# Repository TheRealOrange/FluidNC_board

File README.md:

# FluidNC_board
board for fluidnc

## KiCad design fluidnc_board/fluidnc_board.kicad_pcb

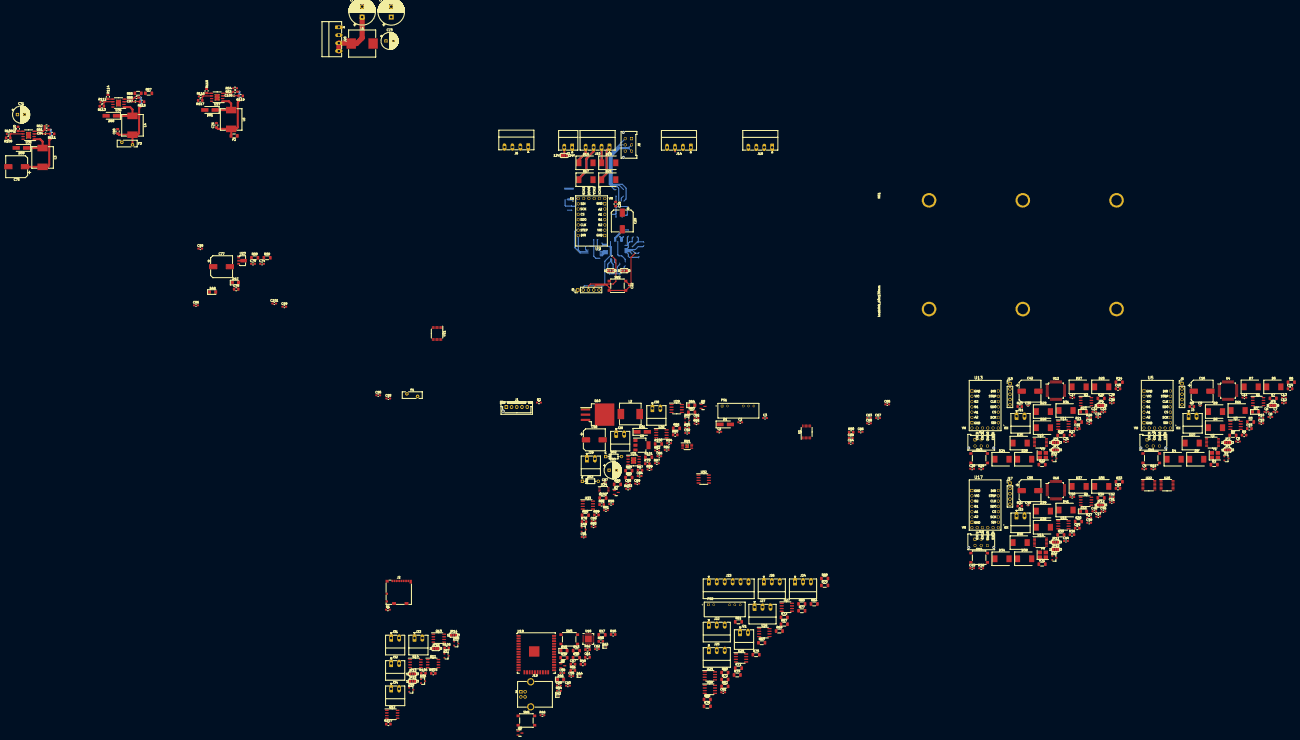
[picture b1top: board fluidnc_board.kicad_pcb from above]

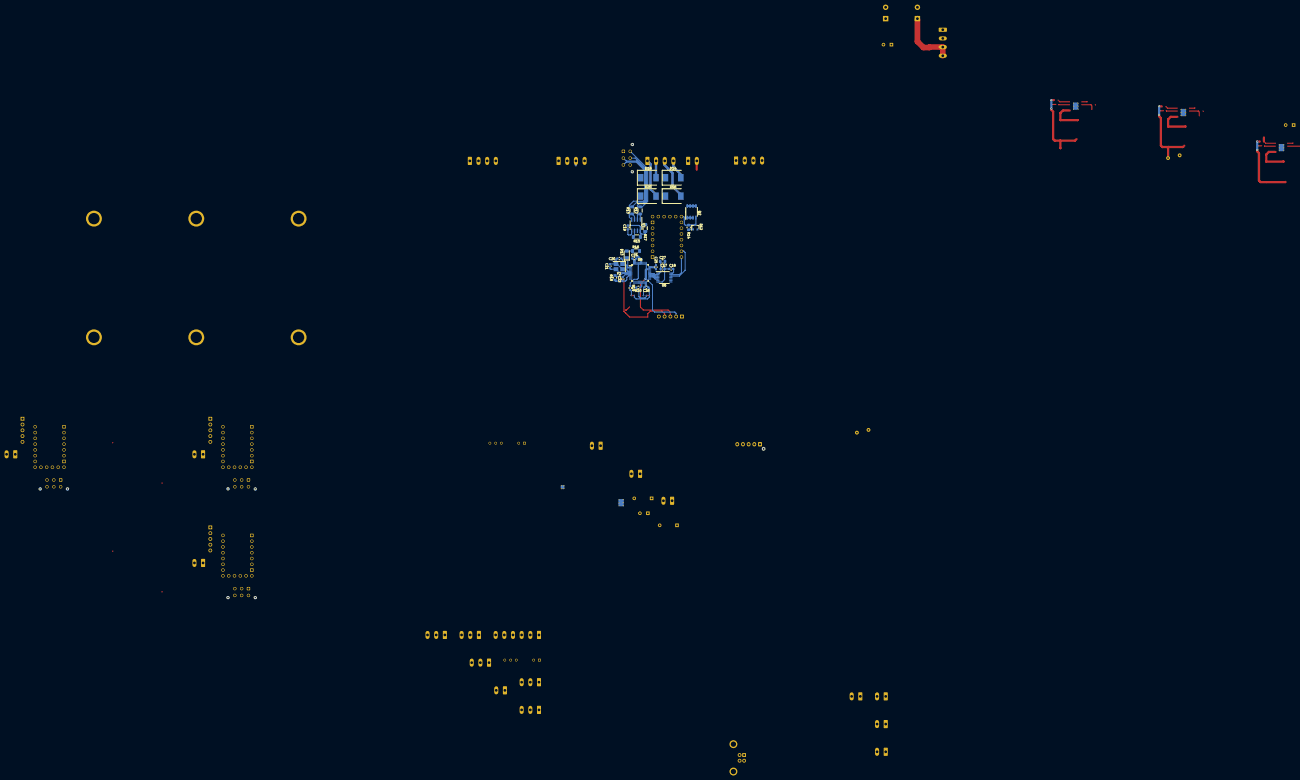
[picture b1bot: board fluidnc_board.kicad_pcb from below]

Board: 4 copper layers, 404 parts (30 on the bottom side), 284 nets.

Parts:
C1, C2, C3, C4, C5, C6, C10, C11, C12, C13, C17, C18, C19, C23, C24, C25, C26, C30, C31, C32, C36, C37, C38, C39, C43, C44, C45, C49, C50, C51, C52, C56, C58, C59, C60, C62, C63, C64, C65, C66, C67, C68, C69, C74, C79, C81, C82, C84, C85, C86, C88, C89, C93, C95, C96, C98, C99, C101: 100n; C_0603_1608Metric_Pad1.08x0.95mm_HandSolder
C7, C8, C20, C21, C33, C34, C46, C47: 22p; C_0603_1608Metric_Pad1.08x0.95mm_HandSolder
C9, C22, C35, C48: 12p; C_0402_1005Metric_Pad0.74x0.62mm_HandSolder
C14, C27, C40, C53: 47u; C_0805_2012Metric_Pad1.18x1.45mm_HandSolder
C15, C28, C41, C54, C57, C61, C76, C78, C80: 4.7u; C_0805_2012Metric_Pad1.18x1.45mm_HandSolder
C16, C29, C42, C55, C75, C77, C90: 100u; CP_Elec_10x10
C70, C72: 470u; CP_Radial_D12.5mm_P5.00mm
C71, C73, C83: 10u; CP_Radial_D8.0mm_P3.50mm
C87, C94, C97, C100: 6.8n; C_0402_1005Metric_Pad0.74x0.62mm_HandSolder
C91, C92: 220p; C_0603_1608Metric_Pad1.08x0.95mm_HandSolder
D1: B360; D_SMA_Handsoldering
D2, D12, D22, D32, D49, D50, D55, D56, D57, D58: BZX84C5V6; D_SOT-23_ANK
D3, D13, D23, D33, D45, D46, D47, D48, D54: LED; LED_1206_3216Metric_Pad1.42x1.75mm_HandSolder
D4, D5, D6, D7, D8, D9, D10, D11, D14, D15, D16, D17, D18, D19, D20, D21, D24, D25, D26, D27, D28, D29, D30, D31, D34, D35, D36, D37, D38, D39, D40, D41: B360; D_SMC
D42, D43, D44: ESD5D5.0C; D_SOD-523
D51, D59, D60, D61: SS2150-LTP; D_SMA_Handsoldering
D52, D53: 1N4148; D_DO-35_SOD27_P7.62mm_Horizontal
F1, F3: 2A; Fuse_Bourns_MF-RHT200
F2: 1A; Fuse_1206_3216Metric_Pad1.42x1.75mm_HandSolder
HS1: heatsink_60x135mm
J1: Conn_01x05_Female; JST_XH_B5B-XH-AM_1x05_P2.50mm_Vertical
J2: Micro_SD_Card_Det; microSD_HC_Molex_104031-0811
J3, J7, J11, J15, J21, J28, J29, J30, J31, J32, J33, J34: Screw_Terminal_01x02; PhoenixContact_MC_1,5_2-G-3.81_1x02_P3.81mm_Horizontal
J4, J8, J12, J16: Conn_01x06_Female; Molex_Micro-Fit_3.0_43045-0612_2x03_P3.00mm_Vertical
J5, J9, J13, J17: SWD; PinHeader_1x05_P2.54mm_Vertical
J6, J10, J14, J18, J20: Screw_Terminal_01x04; PhoenixContact_MC_1,5_4-G-3.81_1x04_P3.81mm_Horizontal
J19: USB_B; USB_B_OST_USB-B1HSxx_Horizontal
J22, J24, J25, J26, J27: Screw_Terminal_01x03; PhoenixContact_MC_1,5_3-G-3.81_1x03_P3.81mm_Horizontal
J23: Screw_Terminal_01x06; PhoenixContact_MC_1,5_6-G-3.81_1x06_P3.81mm_Horizontal
JP1, JP4, JP7, JP10, JP13, JP14, JP15, JP16: SolderJumper_3_Open; SolderJumper-3_P1.3mm_Open_RoundedPad1.0x1.5mm_NumberLabels
JP2, JP3, JP5, JP6, JP8, JP9, JP11, JP12: SolderJumper_3_Bridged12; SolderJumper-3_P1.3mm_Bridged12_RoundedPad1.0x1.5mm_NumberL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
L1: 13u; L_Wuerth_HCI-1365
L2, L3, L4, L5: 33u; L_Vishay_IHLP-4040
PS1: RKZ-2405S; CONV_RKZ
PS2: RKZ-1212S_P; CONV_RKZ
Q1, Q2, Q3, Q4, Q11, Q12, Q13, Q14: IRF7809AVTRPBF; SO-8_3.9x4.9mm_P1.27mm
Q5, Q6: SS8050-G; SOT-23
Q7, Q8: BSS127S; SOT-23
Q9: ZVN4306GTA; SOT-223-3_TabPin2
Q10: IRF9Z24SPBF; TO-263-3_TabPin2
R1, R2, R53, R91, R94: 3k; R_0603_1608Metric_Pad0.98x0.95mm_HandSolder
R3, R4, R12, R13, R21, R22, R30, R31, R56, R57, R58, R100: 270; R_1206_3216Metric_Pad1.30x1.75mm_HandSolder
R5, R9, R14, R18, R23, R27, R32, R36, R41, R42, R48, R49, R50, R81, R89, R104, R105, R106, R107, R109, R111, R113, R115, R117, R119: 10k; R_0805_2012Metric_Pad1.20x1.40mm_HandSolder
R6, R8, R15, R17, R24, R26, R33, R35, R60, R61, R62, R63, R64, R65, R66, R67, R68, R69, R70, R71, R72, R73, R74, R75, R76, R77, R83, R84, R85, R86, R88, R90: 1k; R_1206_3216Metric_Pad1.30x1.75mm_HandSolder
R7, R16, R25, R34, R43, R47, R59, R101, R102: 100; R_1206_3216Metric_Pad1.30x1.75mm_HandSolder
R10, R11, R19, R20, R28, R29, R37, R38, R108, R112, R116: 100k; R_0603_1608Metric_Pad0.98x0.95mm_HandSolder
R39, R40: 0; R_1206_3216Metric_Pad1.30x1.75mm_HandSolder
R44: 22k; R_0603_1608Metric_Pad0.98x0.95mm_HandSolder
R45, R87, R110, R114, R118: 47k; R_0805_2012Metric_Pad1.20x1.40mm_HandSolder
R46, R51, R82: 2.2k; R_0603_1608Metric_Pad0.98x0.95mm_HandSolder
R52: 200; R_0603_1608Metric_Pad0.98x0.95mm_HandSolder
R54, R92: 750; R_0603_1608Metric_Pad0.98x0.95mm_HandSolder
R55, R93: 12k; R_0603_1608Metric_Pad0.98x0.95mm_HandSolder
R78, R79, R80: 150; R_0805_2012Metric_Pad1.20x1.40mm_HandSolder
R95, R96: 30k; R_0603_1608Metric_Pad0.98x0.95mm_HandSolder
R97, R98: 24k; R_0603_1608Metric_Pad0.98x0.95mm_HandSolder
R99: 250; R_0603_1608Metric_Pad0.98x0.95mm_HandSolder
R103: 22; R_0603_1608Metric_Pad0.98x0.95mm_HandSolder
RN1: LT5400_10k; MSOP-8-1EP_3x3mm_P0.65mm_EP1.68x1.88mm_ThermalVias
SW1, SW2, SW3, SW4, SW5, SW6: SW_Push; SW_Push_1P1T_NO_6x6mm_H9.5mm
U1, U2, U6, U10, U14: ADG3304; TSSOP-14_4.4x5mm_P0.65mm
U3, U7, U11, U15, U24, U25, U26, U27, U28, U29, U30: HCPL-0630; SOIC-8_3.9x4.9mm_P1.27mm
U4, U8, U12, U16: STM32F103C8Tx; LQFP-48_7x7mm_P0.5mm
U5, U9, U13, U17: TMC5160_SILENTSTEPSTICK
U18: CP2102N-Axx-xQFN28; QFN-28-1EP_5x5mm_P0.5mm_EP3.35x3.35mm
U19: ESP32-WROOM-32UE; ESP32-WROOM-32U
U20, U21, U22: 74HCT595; TSSOP-16_4.4x5mm_P0.65mm
U23: AZ1117-3.3; SOT-89-3
U31, U35, U36, U37: BD9G341AEFJ; HTSOP-8-1EP_3.9x4.9mm_P1.27mm_EP2.4x3.2mm_ThermalVias
U32, U33: LMV358; SOIC-8_3.9x4.9mm_P1.27mm
U34: OPA2182; TSSOP-8_3x3mm_P0.65mm
Y1, Y2, Y3, Y4: 8M; Crystal_SMD_3225-4Pin_3.2x2.5mm_HandSoldering

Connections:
+3V3: C1.2, C4.2, C6.2, C10.1, C11.1, C12.1, C13.1, C14.1, C17.2, C19.2, C23.1, C24.1, C25.1, C26.1, C27.1, C30.2, C32.2, C36.1, C37.1, C38.1, C39.1, C40.1, C43.2, C45.2, C49.1, C50.1, C51.1, C52.1, C53.1, C56.1, C57.1, C61.1, C62.1, C78.1, C79.1, J1.4, J2.4 (VDD), J5.5, J9.5, J13.5, J17.5, JP2.1 (A), JP3.1 (A), JP5.1 (A), JP6.1 (A), JP8.1 (A), JP9.1 (A), JP11.1 (A), JP12.1 (A), R1.1, R2.1, R6.1, R7.1, R8.1, R9.1, R15.1, R16.1, R17.1, R18.1, R24.1, R25.1, R26.1, R27.1, R33.1, R34.1, R35.1, R36.1, R43.1, R46.1, R47.1, R49.1, R59.2, R65.1, R66.1, R67.1, R68.1, R69.1, R74.1, R75.1, R76.1, R77.1, R78.2, R79.2, R80.2, U1.1 (VCCA), U1.8 (EN), U2.1 (VCCA), U2.8 (EN), U3.8 (VCC), U4.9 (VDDA), U4.24 (VDD), U4.36 (VDD), U4.48 (VDD), U6.1 (VCCA), U6.8 (EN), U7.8 (VCC), U8.9 (VDDA), U8.24 (VDD), U8.36 (VDD), U8.48 (VDD), U10.1 (VCCA), U10.8 (EN), U11.8 (VCC), U12.9 (VDDA), U12.24 (VDD), U12.36 (VDD), U12.48 (VDD), U14.1 (VCCA), U14.8 (EN), U15.8 (VCC), U16.9 (VDDA), U16.24 (VDD), U16.36 (VDD), U16.48 (VDD), U18.6 (VDD), U18.7 (VREGIN), U19.2 (VDD), U23.2 (VO), U24.8 (VCC), U25.8 (VCC), U26.8 (VCC), U27.8 (VCC), U28.8 (VCC)
+5V: C2.1, C5.1, C18.1, C31.1, C44.1, C63.1, C64.1, C65.1, C66.1, C67.1, C68.1, C69.1, D1.2 (A), F2.1, J1.5, PS1.1 (+VIN), R58.2, U1.14 (VCCY), U2.14 (VCCY), U5.10 (VIO), U6.14 (VCCY), U9.10 (VIO), U10.14 (VCCY), U13.10 (VIO), U14.14 (VCCY), U17.10 (VIO), U20.16 (VCC), U21.16 (VCC), U22.16 (VCC)
+12V: F1.1, JP1.1 (A), JP4.1 (A), JP7.1 (A), JP10.1 (A), JP13.1 (A), JP14.1 (A), JP15.1 (A), JP16.1 (A), PS2.1 (+VIN)
+24V: F3.1, JP1.3 (B), JP4.3 (B), JP7.3 (B), JP10.3 (B), JP13.3 (B), JP14.3 (B), JP15.3 (B), JP16.3 (B)
+48V: C15.1, C16.1, C28.1, C29.1, C41.1, C42.1, C54.1, C55.1, C71.1, C72.1, C73.1, C74.1, C77.1, C93.1, C96.1, C99.1, D1.1 (K), D4.1 (K), D6.1 (K), D8.1 (K), D10.1 (K), D14.1 (K), D16.1 (K), D18.1 (K), D20.1 (K), D24.1 (K), D26.1 (K), D28.1 (K), D30.1 (K), D34.1 (K), D36.1 (K), D38.1 (K), D40.1 (K), L1.2, R108.1, R112.1, R116.1, U5.16 (VM), U9.16 (VM), U13.16 (VM), U17.16 (VM), U23.3 (VI), U35.8 (VCC), U36.8 (VCC), U37.8 (VCC)
/CS_E: U17.4 (CSN), U20.3 (QD)
/CS_X: U5.4 (CSN), U22.7 (QH)
/CS_Y: U9.4 (CSN), U22.3 (QD)
/CS_Z: U13.4 (CSN), U20.7 (QH)
/DIR_E: U14.10 (Y4), U20.1 (QB)
/DIR_X: U2.10 (Y4), U22.5 (QF)
/DIR_Y: U6.10 (Y4), U22.1 (QB)
/DIR_Z: U10.10 (Y4), U20.5 (QF)
/EN_E: D32.1 (K), Q4.4, R32.1, U17.1 (EN), U20.15 (QA)
/EN_X: D2.1 (K), Q1.4, R5.1, U5.1 (EN), U22.4 (QE)
/EN_Y: D12.1 (K), Q2.4, R14.1, U9.1 (EN), U22.15 (QA)
/EN_Z: D22.1 (K), Q3.4, R23.1, U13.1 (EN), U20.4 (QE)
/I2S_BCK: R50.1, U19.36 (IO22), U20.11 (SRCLK), U21.11 (SRCLK), U22.11 (SRCLK)
/I2S_DATA: U19.33 (IO21), U20.14 (SER)
/I2S_WS: U19.28 (IO17), U20.12 (RCLK), U21.12 (RCLK), U22.12 (RCLK)
/MISO: J2.7 (DAT0), U1.3 (A2), U19.31 (IO19)
/MOSI: J2.3 (CMD), U1.2 (A1), U19.37 (IO23)
/SCK: J2.5 (CLK), U1.4 (A3), U19.30 (IO18)
/SCL: J1.2, R2.2, U19.14 (IO12)
/SDA: J1.3, R1.2, U19.23 (IO15)
/SD_CS: J2.2 (DAT3/CD), U19.29 (IO5)
/STEP_E: U14.11 (Y3), U20.2 (QC)
/STEP_X: U2.11 (Y3), U22.6 (QG)
/STEP_Y: U6.11 (Y3), U22.2 (QC)
/STEP_Z: U10.11 (Y3), U20.6 (QG)
/esp32/D+: D43.2 (A2), J19.3 (D+), U18.4 (D+)
/esp32/D-: D44.2 (A2), J19.2 (D-), U18.5 (D-)
/esp32/DTR: Q6.2 (E), R41.1, U18.28 (~DTR)
/esp32/EN: C58.1, C60.2, Q5.3 (C), R49.2, SW6.2, U19.3 (EN)
/esp32/IO0: C59.2, Q6.3 (C), SW5.2
/esp32/LIM_E: R77.2, U19.4 (SENSOR_VP), U28.6 (VO2)
/esp32/LIM_X: R74.2, U19.7 (IO35), U27.7 (VO1)
/esp32/LIM_Y: R76.2, U19.6 (IO34), U27.6 (VO2)
/esp32/LIM_Z: R75.2, U19.5 (SENSOR_VN), U28.7 (VO1)
/esp32/RTS: Q5.2 (E), R42.1, U18.24 (~RTS)
/esp32/RXD: R39.1, U18.25 (RXD)
/esp32/RXD0: R40.2, U19.34 (RXD0/IO3)
/esp32/RXT: D46.1 (K), U18.18 (~RXT/GPIO.1)
/esp32/SPINDLE_DIR: U19.9 (IO33), U30.4 (A2)
/esp32/SPINDLE_EN: U19.8 (IO32), U30.2 (C1)
/esp32/SPINDLE_PWM: U19.24 (IO2), U29.2 (C1)
/esp32/TXD: R40.1, U18.26 (TXD)
/esp32/TXD0: R39.2, U19.35 (TXD0/IO1)
/esp32/TXT: D45.1 (K), U18.19 (~TXT/GPIO.0)
/esp32/VUSB: D42.2 (A2), J19.1 (VBUS), R44.1
/i2so/ISO16: D56.1 (K), Q12.4, R105.1, U21.15 (QA)
/i2so/ISO17: D55.1 (K), Q11.4, R104.1, U21.1 (QB)
/i2so/ISO18: D57.1 (K), Q13.4, R106.1, U21.2 (QC)
/i2so/ISO19: D58.1 (K), Q14.4, R107.1, U21.3 (QD)
/motor_drivers/5V_ISO+: C3.1, J4.6, J8.6, J12.6, J16.6, PS1.7 (+VOUT)
/motor_drivers/5V_ISO-: C3.2, J4.1, J8.1, J12.1, J16.1, PS1.5 (-VOUT)
/motor_drivers/MISO_5V: U1.12 (Y2), U5.5 (SDO), U9.5 (SDO), U13.5 (SDO), U17.5 (SDO)
/motor_drivers/MOSI_5V: U1.13 (Y1), U5.2 (SDI), U9.2 (SDI), U13.2 (SDI), U17.2 (SDI)
/motor_drivers/SCK_5V: U1.11 (Y3), U5.3 (SCK), U9.3 (SCK), U13.3 (SCK), U17.3 (SCK)
/motor_drivers/driver_e/BOOT0: JP11.2 (C), R37.2
/motor_drivers/driver_e/BOOT1: JP12.2 (C), R38.2
/motor_drivers/driver_e/DIR_3V3: U14.5 (A4), U16.27 (PB14)
/motor_drivers/driver_e/DIR_DRV: U14.13 (Y1), U17.8 (DIR)
/motor_drivers/driver_e/DIR_DRV_3V3: U14.2 (A1), U16.30 (PA9)
/motor_drivers/driver_e/ENC_A: R35.2, U15.7 (VO1), U16.41 (PB5)
/motor_drivers/driver_e/ENC_B: R33.2, U15.6 (VO2), U16.42 (PB6)
/motor_drivers/driver_e/LED_IND: D33.1 (K), U16.2 (PC13)
/motor_drivers/driver_e/NRST: C48.1, J17.4, R36.2, SW4.2, U16.7 (NRST)
/motor_drivers/driver_e/STEP_3V3: U14.4 (A3), U16.28 (PB15)
/motor_drivers/driver_e/STEP_DRV: U14.12 (Y2), U17.7 (STEP)
/motor_drivers/driver_e/STEP_DRV_3V3: U14.3 (A2), U16.29 (PA8)
/motor_drivers/driver_e/SWCLK: J17.3, U16.37 (PA14)
/motor_drivers/driver_e/SWDIO: J17.2, U16.34 (PA13)
/motor_drivers/driver_x/BOOT0: JP2.2 (C), R10.2
/motor_drivers/driver_x/BOOT1: JP3.2 (C), R11.2
/motor_drivers/driver_x/DIR_3V3: U2.5 (A4), U4.27 (PB14)
/motor_drivers/driver_x/DIR_DRV: U2.13 (Y1), U5.8 (DIR)
/motor_drivers/driver_x/DIR_DRV_3V3: U2.2 (A1), U4.30 (PA9)
/motor_drivers/driver_x/ENC_A: R8.2, U3.7 (VO1), U4.41 (PB5)
/motor_drivers/driver_x/ENC_B: R6.2, U3.6 (VO2), U4.42 (PB6)
/motor_drivers/driver_x/LED_IND: D3.1 (K), U4.2 (PC13)
/motor_drivers/driver_x/NRST: C9.1, J5.4, R9.2, SW1.2, U4.7 (NRST)
/motor_drivers/driver_x/STEP_3V3: U2.4 (A3), U4.28 (PB15)
/motor_drivers/driver_x/STEP_DRV: U2.12 (Y2), U5.7 (STEP)
/motor_drivers/driver_x/STEP_DRV_3V3: U2.3 (A2), U4.29 (PA8)
/motor_drivers/driver_x/SWCLK: J5.3, U4.37 (PA14)
/motor_drivers/driver_x/SWDIO: J5.2, U4.34 (PA13)
/motor_drivers/driver_y/BOOT0: JP5.2 (C), R19.2
/motor_drivers/driver_y/BOOT1: JP6.2 (C), R20.2
/motor_drivers/driver_y/DIR_3V3: U6.5 (A4), U8.27 (PB14)
/motor_drivers/driver_y/DIR_DRV: U6.13 (Y1), U9.8 (DIR)
/motor_drivers/driver_y/DIR_DRV_3V3: U6.2 (A1), U8.30 (PA9)
/motor_drivers/driver_y/ENC_A: R17.2, U7.7 (VO1), U8.41 (PB5)
/motor_drivers/driver_y/ENC_B: R15.2, U7.6 (VO2), U8.42 (PB6)
/motor_drivers/driver_y/LED_IND: D13.1 (K), U8.2 (PC13)
/motor_drivers/driver_y/NRST: C22.1, J9.4, R18.2, SW2.2, U8.7 (NRST)
/motor_drivers/driver_y/STEP_3V3: U6.4 (A3), U8.28 (PB15)
/motor_drivers/driver_y/STEP_DRV: U6.12 (Y2), U9.7 (STEP)
/motor_drivers/driver_y/STEP_DRV_3V3: U6.3 (A2), U8.29 (PA8)
/motor_drivers/driver_y/SWCLK: J9.3, U8.37 (PA14)
/motor_drivers/driver_y/SWDIO: J9.2, U8.34 (PA13)
/motor_drivers/driver_z/BOOT0: JP8.2 (C), R28.2
/motor_drivers/driver_z/BOOT1: JP9.2 (C), R29.2
/motor_drivers/driver_z/DIR_3V3: U10.5 (A4), U12.27 (PB14)
/motor_drivers/driver_z/DIR_DRV: U10.13 (Y1), U13.8 (DIR)
/motor_drivers/driver_z/DIR_DRV_3V3: U10.2 (A1), U12.30 (PA9)
/motor_drivers/driver_z/ENC_A: R26.2, U11.7 (VO1), U12.41 (PB5)
/motor_drivers/driver_z/ENC_B: R24.2, U11.6 (VO2), U12.42 (PB6)
/motor_drivers/driver_z/LED_IND: D23.1 (K), U12.2 (PC13)
/motor_drivers/driver_z/NRST: C35.1, J13.4, R27.2, SW3.2, U12.7 (NRST)
/motor_drivers/driver_z/STEP_3V3: U10.4 (A3), U12.28 (PB15)
/motor_drivers/driver_z/STEP_DRV: U10.12 (Y2), U13.7 (STEP)
/motor_drivers/driver_z/STEP_DRV_3V3: U10.3 (A2), U12.29 (PA8)
/motor_drivers/driver_z/SWCLK: J13.3, U12.37 (PA14)
/motor_drivers/driver_z/SWDIO: J13.2, U12.34 (PA13)
/power_supply/regulator1/FB: R55.2, R56.1, U36.4 (FB)
/power_supply/regulator1/OUT: C80.1, F3.2, L4.2, R55.1
/power_supply/regulator2/FB: R53.2, R54.1, U37.4 (FB)
/power_supply/regulator2/OUT: C76.1, F2.2, L5.2, R53.1
/power_supply/regulator/FB: R51.2, R52.1, U35.4 (FB)
/power_supply/regulator/OUT: C75.1, F1.2, L3.2, R51.1
/spindle_cntrl/1V_REF: R97.1, U33.1, U33.2 (-)
/spindle_cntrl/5V: C84.1, C90.1, L2.2, R83.1, R84.1, R86.1, R91.1, R93.1, R100.2, U29.8 (VCC), U30.8 (VCC), U32.8 (V+), U33.8 (V+)
/spindle_cntrl/24V_VFD: C82.1, C83.1, D52.1 (K), J28.2, R81.1, R99.1, RN1.8 (R1.2), U31.8 (VCC), U34.8 (V+)
/switches/12V_ISO+: C81.1, J22.3, J24.3, J25.3, J26.3, J27.3, PS2.7 (+VOUT), R60.1, R61.1, R62.1, R63.1, R64.1, R70.1, R71.1, R72.1, R73.1
/switches/12V_ISO-: C81.2, J21.1, J22.1, J23.1, J23.3, J23.5, J24.1, J25.1, J26.1, J27.1, PS2.5 (-VOUT)
/switches/ABRT: J23.2, R66.2, U19.12 (IO27), U25.2 (C1), U25.7 (VO1)
/switches/DOOR: J21.2, R69.2, U19.16 (IO13), U25.3 (C2), U25.6 (VO2)
/switches/HOLD: J23.4, R68.2, U19.10 (IO25), U24.3 (C2), U24.6 (VO2)
/switches/LIM_E_IXO: J27.2, U28.3 (C2)
/switches/LIM_X_ISO: J24.2, U27.2 (C1)
/switches/LIM_Z_ISO: J26.2, U28.2 (C1)
/switches/PROBE: J22.2, R67.2, U19.13 (IO14), U26.2 (C1), U26.7 (VO1)
/switches/START: J23.6, R65.2, U19.11 (IO26), U24.2 (C1), U24.7 (VO1)
GND: C1.1, C2.2, C4.1, C5.2, C6.1, C7.2, C8.2, C9.2, C10.2, C11.2, C12.2, C13.2, C14.2, C15.2, C16.2, C17.1, C18.2, C19.1, C20.2, C21.2, C22.2, C23.2, C24.2, C25.2, C26.2, C27.2, C28.2, C29.2, C30.1, C31.2, C32.1, C33.2, C34.2, C35.2, C36.2, C37.2, C38.2, C39.2, C40.2, C41.2, C42.2, C43.1, C44.2, C45.1, C46.2, C47.2, C48.2, C49.2, C50.2, C51.2, C52.2, C53.2, C54.2, C55.2, C56.2, C57.2, C58.2, C59.1, C60.1, C61.2, C62.2, C63.2, C64.2, C65.2, C66.2, C67.2, C68.2, C69.2, C70.2, C71.2, C72.2, C73.2, C74.2, C75.2, C76.2, C77.2, C78.2, C79.2, C80.2, C82.2, C83.2, C84.2, C85.2, C86.2, C89.2, C90.2, C93.2, C96.2, C99.2, D2.2 (A), D5.2 (A), D7.2 (A), D9.2 (A), D11.2 (A), D12.2 (A), D15.2 (A), D17.2 (A), D19.2 (A), D21.2 (A), D22.2 (A), D25.2 (A), D27.2 (A), D29.2 (A), D31.2 (A), D32.2 (A), D35.2 (A), D37.2 (A), D39.2 (A), D41.2 (A), D42.1 (A1), D43.1 (A1), D44.1 (A1), D47.1 (K), D48.1 (K), D49.2 (A), D50.2 (A), D51.2 (A), D53.2 (A), D54.1 (K), D55.2 (A), D56.2 (A), D57.2 (A), D58.2 (A), D59.2 (A), D60.2 (A), D61.2 (A), J1.1, J2.6 (VSS), J2.11 (SHIELD), J5.1, J9.1, J13.1, J17.1, J19.4 (GND), J19.5 (Shield), J20.1, J20.2, J28.1, J30.1, JP2.3 (B), JP3.3 (B), JP5.3 (B), JP6.3 (B), JP8.3 (B), JP9.3 (B), JP11.3 (B), JP12.3 (B), PS1.2 (-VIN), PS2.2 (-VIN), Q1.1, Q1.2, Q1.3, Q2.1, Q2.2, Q2.3, Q3.1, Q3.2, Q3.3, Q4.1, Q4.2, Q4.3, Q7.2 (S), Q8.2 (S), Q11.1, Q11.2, Q11.3, Q12.1, Q12.2, Q12.3, Q13.1, Q13.2, Q13.3, Q14.1, Q14.2, Q14.3, R5.2, R14.2, R23.2, R32.2, R45.2, R48.2, R50.2, R52.2, R54.2, R57.2, R82.2, R87.2, R89.2, R92.2, R94.2, R96.2, R104.2, R105.2, R106.2, R107.2, R109.2, R110.2, R111.2, R113.2, R114.2, R115.2, R117.2, R118.2, R119.2, RN1.2 (R2.1), SW1.1, SW2.1, SW3.1, SW4.1, SW5.1, SW6.1, U1.7 (GND), U2.7 (GND), U3.5 (GND), U4.8 (VSSA), U4.23 (VSS), U4.35 (VSS), U4.47 (VSS), U5.6 (CLK), U5.9 (GND), U5.15 (GND), U6.7 (GND), U7.5 (GND), U8.8 (VSSA), U8.23 (VSS), U8.35 (VSS), U8.47 (VSS), U9.6 (CLK), U9.9 (GND), U9.15 (GND), U10.7 (GND), U11.5 (GND), U12.8 (VSSA), U12.23 (VSS), U12.35 (VSS), U12.47 (VSS), U13.6 (CLK), U13.9 (GND), U13.15 (GND), U14.7 (GND), U15.5 (GND), U16.8 (VSSA), U16.23 (VSS), U16.35 (VSS), U16.47 (VSS), U17.6 (CLK), U17.9 (GND), U17.15 (GND), U18.3 (GND), U18.29 (GND), U19.1 (GND), U19.15 (GND), U19.38 (GND), U19.39 (GND), U20.8 (GND), U20.13 (~OE), U21.8 (GND), U21.13 (~OE), U22.8 (GND), U22.13 (~OE), U23.1 (GND), U24.5 (GND), U25.5 (GND), U26.5 (GND), U27.5 (GND), U28.5 (GND), U29.5 (GND), U30.5 (GND), U31.2 (GND), U31.9 (GND), U32.4 (V-), U33.4 (V-), U34.4 (V-), U35.2 (GND), U35.9 (GND), U36.2 (GND), U36.9 (GND), U37.2 (GND), U37.9 (GND), Y1.2, Y1.4, Y2.2, Y2.4, Y3.2, Y3.4, Y4.2, Y4.4
unnamed: C7.1, U4.5 (PD0), Y1.1
unnamed: C8.1, U4.6 (PD1), Y1.3
unnamed: C20.1, U8.5 (PD0), Y2.1
unnamed: C21.1, U8.6 (PD1), Y2.3
unnamed: C33.1, U12.5 (PD0), Y3.1
unnamed: C34.1, U12.6 (PD1), Y3.3
unnamed: C46.1, U16.5 (PD0), Y4.1
unnamed: C47.1, U16.6 (PD1), Y4.3
unnamed: C70.1, J20.3, J20.4, L1.1
unnamed: C85.1, R85.1, R88.2
unnamed: C86.1, R88.1, R90.2
unnamed: C87.1, U31.3 (VC)
unnamed: C87.2, R89.1
unnamed: C88.1, U31.7 (BST)
unnamed: C88.2, D51.1 (K), L2.1, U31.1 (LX)
unnamed: C89.1, R90.1, U32.5 (+)
unnamed: C91.1, Q9.3 (S), RN1.7 (R2.2), U34.2 (A-)
unnamed: C91.2, R101.2, U34.1 (OUT_A)
unnamed: C92.1, R102.2, U34.7 (OUT_B)
unnamed: C92.2, Q10.3 (S), R99.2, U34.6 (B-)
unnamed: C94.1, U35.3 (VC)
unnamed: C94.2, R111.1
unnamed: C95.1, U35.7 (BST)
unnamed: C95.2, D59.1 (K), L3.1, U35.1 (LX)
unnamed: C97.1, U36.3 (VC)
unnamed: C97.2, R115.1
unnamed: C98.1, U36.7 (BST)
unnamed: C98.2, D60.1 (K), L4.1, U36.1 (LX)
unnamed: C100.1, U37.3 (VC)
unnamed: C100.2, R119.1
unnamed: C101.1, U37.7 (BST)
unnamed: C101.2, D61.1 (K), L5.1, U37.1 (LX)
unnamed: D3.2 (A), R7.2
unnamed: D4.2 (A), D5.1 (K), J6.4, U5.14 (OA2)
unnamed: D6.2 (A), D7.1 (K), J6.3, U5.13 (OA1)
unnamed: D8.2 (A), D9.1 (K), J6.2, U5.12 (OB1)
unnamed: D10.2 (A), D11.1 (K), J6.1, U5.11 (OB2)
unnamed: D13.2 (A), R16.2
unnamed: D14.2 (A), D15.1 (K), J10.4, U9.14 (OA2)
unnamed: D16.2 (A), D17.1 (K), J10.3, U9.13 (OA1)
unnamed: D18.2 (A), D19.1 (K), J10.2, U9.12 (OB1)
unnamed: D20.2 (A), D21.1 (K), J10.1, U9.11 (OB2)
unnamed: D23.2 (A), R25.2
unnamed: D24.2 (A), D25.1 (K), J14.4, U13.14 (OA2)
unnamed: D26.2 (A), D27.1 (K), J14.3, U13.13 (OA1)
unnamed: D28.2 (A), D29.1 (K), J14.2, U13.12 (OB1)
unnamed: D30.2 (A), D31.1 (K), J14.1, U13.11 (OB2)
unnamed: D33.2 (A), R34.2
unnamed: D34.2 (A), D35.1 (K), J18.4, U17.14 (OA2)
unnamed: D36.2 (A), D37.1 (K), J18.3, U17.13 (OA1)
unnamed: D38.2 (A), D39.1 (K), J18.2, U17.12 (OB1)
unnamed: D40.2 (A), D41.1 (K), J18.1, U17.11 (OB2)
unnamed: D45.2 (A), R43.2
unnamed: D46.2 (A), R47.2
unnamed: D47.2 (A), R58.1
unnamed: D48.2 (A), R59.1
unnamed: D49.1 (K), Q7.1 (G), R86.2, U30.7 (VO1)
unnamed: D50.1 (K), Q8.1 (G), R84.2, U30.6 (VO2)
unnamed: D52.2 (A), D53.1 (K), Q10.2 (D), R103.1
unnamed: D54.2 (A), R100.1
unnamed: J3.1, Q1.5, Q1.6, Q1.7, Q1.8
unnamed: J3.2, JP1.2 (C)
unnamed: J4.2, R4.2
unnamed: J7.1, Q2.5, Q2.6, Q2.7, Q2.8
unnamed: J7.2, JP4.2 (C)
unnamed: J8.2, R13.2
unnamed: J11.1, Q3.5, Q3.6, Q3.7, Q3.8
unnamed: J11.2, JP7.2 (C)
unnamed: J12.2, R22.2
unnamed: J15.1, Q4.5, Q4.6, Q4.7, Q4.8
unnamed: J15.2, JP10.2 (C)
unnamed: J16.2, R31.2
unnamed: J29.1, Q7.3 (D)
unnamed: J29.2, Q8.3 (D)
unnamed: J30.2, R103.2
unnamed: J31.1, Q11.5, Q11.6, Q11.7, Q11.8
unnamed: J31.2, JP13.2 (C)
unnamed: J32.1, Q12.5, Q12.6, Q12.7, Q12.8
unnamed: J32.2, JP14.2 (C)
unnamed: J33.1, Q13.5, Q13.6, Q13.7, Q13.8
unnamed: J33.2, JP15.2 (C)
unnamed: J34.1, Q14.5, Q14.6, Q14.7, Q14.8
unnamed: J34.2, JP16.2 (C)
unnamed: Q5.1 (B), R41.2
unnamed: Q6.1 (B), R42.2
unnamed: Q9.1 (G), R101.1
unnamed: Q9.2 (D), RN1.1 (R1.1), U34.5 (B+)
unnamed: Q10.1 (G), R102.1
unnamed: R3.1, U3.1 (A1)
unnamed: J4.4, R3.2
unnamed: R4.1, U3.3 (C2)
unnamed: R10.1, U4.44 (BOOT0)
unnamed: R11.1, U4.20 (PB2)
unnamed: R12.1, U7.1 (A1)
unnamed: J8.4, R12.2
unnamed: R13.1, U7.3 (C2)
unnamed: R19.1, U8.44 (BOOT0)
unnamed: R20.1, U8.20 (PB2)
unnamed: R21.1, U11.1 (A1)
unnamed: J12.4, R21.2
unnamed: R22.1, U11.3 (C2)
unnamed: R28.1, U12.44 (BOOT0)
unnamed: R29.1, U12.20 (PB2)
unnamed: R30.1, U15.1 (A1)
unnamed: J16.4, R30.2
unnamed: R31.1, U15.3 (C2)
unnamed: R37.1, U16.44 (BOOT0)
unnamed: R38.1, U16.20 (PB2)
unnamed: R44.2, R45.1, U18.8 (VBUS)
unnamed: R46.2, U18.9 (~RST)
unnamed: R48.1, U18.11 (~SUSPEND)
unnamed: R56.2, R57.1
unnamed: R60.2, U24.1 (A1)
unnamed: R61.2, U24.4 (A2)
unnamed: R62.2, U25.1 (A1)
unnamed: R63.2, U25.4 (A2)
unnamed: R64.2, U26.1 (A1)
unnamed: R70.2, U27.1 (A1)
unnamed: R71.2, U27.4 (A2)
unnamed: R72.2, U28.1 (A1)
unnamed: R73.2, U28.4 (A2)
unnamed: R78.1, U29.1 (A1)
unnamed: R79.1, U30.1 (A1)
unnamed: R80.1, U30.3 (C2)
unnamed: R81.2, R82.1, U31.6 (EN)
unnamed: R83.2, R85.2, U29.7 (VO1)
unnamed: R87.1, U31.5 (RT)
unnamed: R91.2, R92.1, U31.4 (FB)
unnamed: R93.2, R94.1, U33.3 (+)
unnamed: R95.1, R97.2, U33.5 (+)
unnamed: R95.2, U32.6 (-), U32.7
unnamed: R96.1, R98.2, U33.6 (-)
unnamed: R98.1, U33.7, U34.3 (A+)
unnamed: R108.2, R109.1, U35.6 (EN)
unnamed: R110.1, U35.5 (RT)
unnamed: R112.2, R113.1, U36.6 (EN)
unnamed: R114.1, U36.5 (RT)
unnamed: R116.2, R117.1, U37.6 (EN)
unnamed: R118.1, U37.5 (RT)
unnamed: J4.5, U3.2 (C1)
unnamed: J4.3, U3.4 (A2)
unnamed: J8.5, U7.2 (C1)
unnamed: J8.3, U7.4 (A2)
unnamed: J12.5, U11.2 (C1)
unnamed: J12.3, U11.4 (A2)
unnamed: J16.5, U15.2 (C1)
unnamed: J16.3, U15.4 (A2)
unnamed: U20.9 (QH'), U22.14 (SER)
unnamed: U21.14 (SER), U22.9 (QH')

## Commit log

2022-01-30 inital commit
2022-02-10 esp32 and motor driver stuff
2022-02-11 outputs, spindle output and switch inputs
2022-02-11 remove unnecessary i2s chip
2022-02-14 footprint associations and part no.
2022-02-14 fix some footprint associations
2022-02-16 fixed some footprint associations, placed footprints
2022-02-16 placed and routed one stepper motor unit
2022-04-29 one driver unit layout
